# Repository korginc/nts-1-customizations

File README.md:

# nts-1-customizations

Official repository for hardware customizations of the [Nu:Tekt NTS-1 digital kit](https://www.korg.com/nts_1) programmable synthesizer. 

Make your own custom interface using reference schematics, CAD and PCB data, and libraries for the Arduino IDE.

## Repo Content

* _Arduino/package_nts1_custom_panels_index.json_: Arduino IDE package Boards Manager package description file
* _Custom_Panel_RevC/_: Content specific to NTS-1 Custom Panel reference board revision C
  * _Arduino/libraries/_: Arduino IDE libraries
  * _Gerber/_: Raw PCB Gerber data output
  * _KiCAD/_: [KiCAD](https://kicad.org/) project
  * _BOM-mouser.pdf_: Bill of materials with [Mouser](https://www.mouser.com/) part numbers in PDF format
  * _BOM-mouser.xls_: Bill of materials with [Mouser](https://www.mouser.com/) part numbers in XLS format (can be uploaded directly to cart)
  * _Gerber\_reference.pdf_: PCB trace and masks visual reference in PDF format
  * _mount\_diagram.pdf_: Part placement visual reference in PDF format
  * _schematic.pdf_: Circuit diagram in PDF format

## Assembly/Programming

Refer to the [companion web site](https://korginc.github.io/nts-1-customizations) for assembly/programming instructions, examples and further reference.

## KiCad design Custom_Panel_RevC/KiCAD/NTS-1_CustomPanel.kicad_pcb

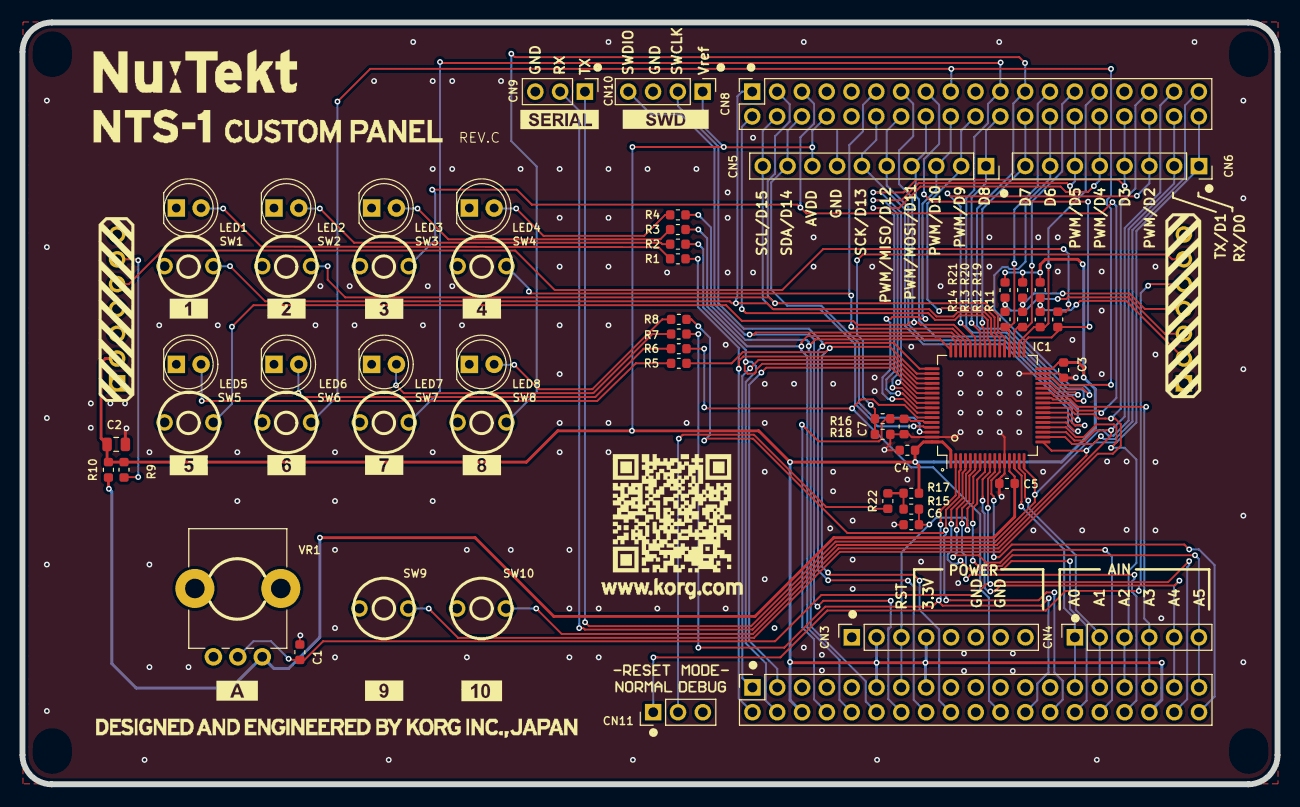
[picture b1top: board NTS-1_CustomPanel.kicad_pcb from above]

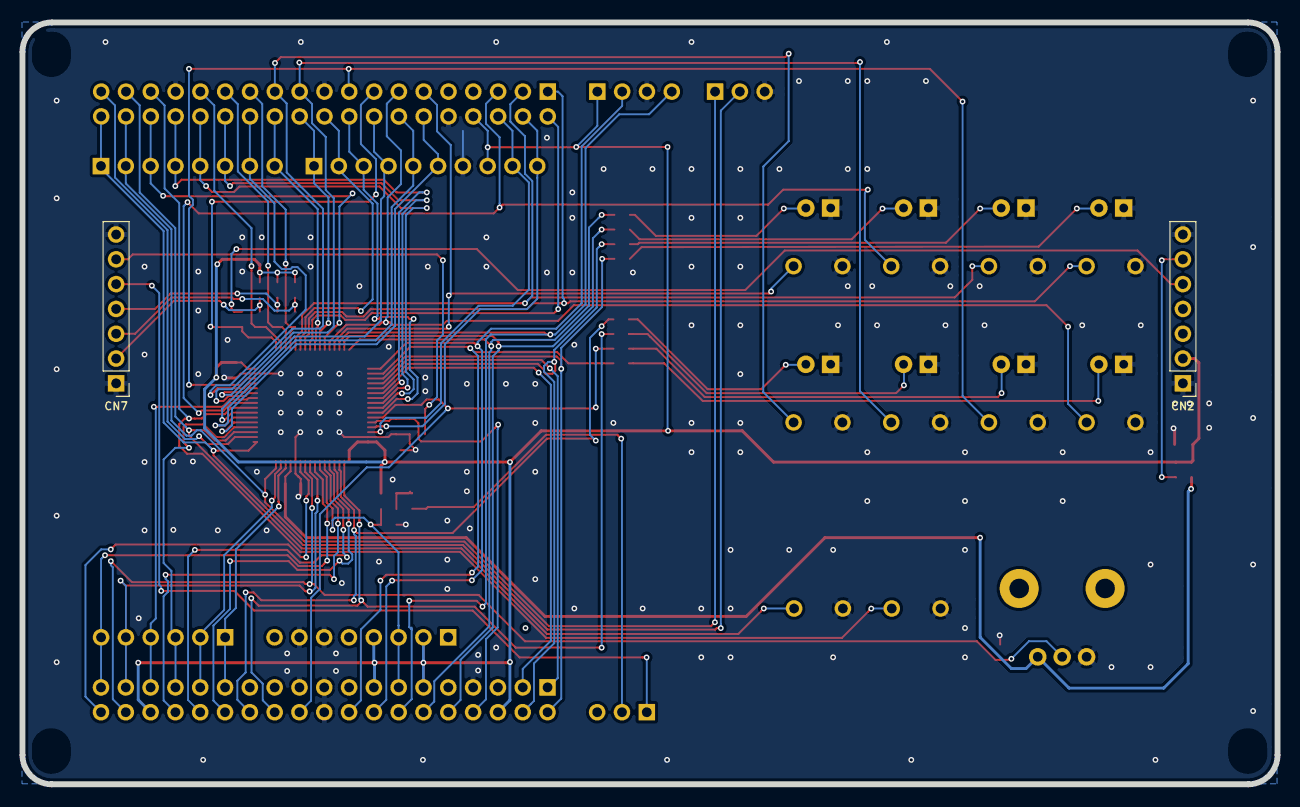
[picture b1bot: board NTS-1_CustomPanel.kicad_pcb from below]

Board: 2 copper layers, 128.5 x 78.0 mm, 60 parts (2 on the bottom side), 77 nets.

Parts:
C1, C3, C4, C5: 0.1u; C_0603_1608Metric
C2: 10u; C_0805_2012Metric
C6, C7: 1000p; C_0603_1608Metric
CN1, CN8: 19x2 2.54mm header; PinSocket_2x19_P2.54mm_Vertical
CN2, CN7: 1x7 2.54mm header; PinHeader_1x07_P2.54mm_Vertical
CN3, CN6: 1x8 2.54mm connector; PinSocket_1x08_P2.54mm_Vertical
CN4: 1x6 2.54mm connector; PinSocket_1x06_P2.54mm_Vertical
CN5: 1x10 2.54mm connector; PinSocket_1x10_P2.54mm_Vertical
CN9, CN11: 1x3 2.54mm header; PinHeader_1x03_P2.54mm_Vertical
CN10: 1x4 2.54mm header; PinHeader_1x04_P2.54mm_Vertical
IC1: STM32F030R8T6; LQFP-64_10x10mm_P0.5mm
LED1, LED2, LED3, LED4, LED5, LED6, LED7, LED8: LED; LED_D5.0mm
R1, R2, R3, R4, R5, R6, R7, R8: 220; R_0603_1608Metric
R9, R19, R20, R21: 10k; R_0603_1608Metric
R10: 0; R_0603_1608Metric
R11, R12, R13, R14: 47; R_0603_1608Metric
R15: 33; R_0603_1608Metric
R16, R22: 1k; R_0603_1608Metric
R17: 100k; R_0603_1608Metric
R18: 47k; R_0603_1608Metric
SW1, SW2, SW3, SW4, SW5, SW6, SW7, SW8, SW9, SW10: TACT SW; SW_Tactile_SKRH
VR1: 10kB; Potentiometer_Alps_RK09K_Single_Vertical

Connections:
+3V3: C2.1, C3.1, C4.1, CN1.6, CN1.11, CN1.15, CN1.34, CN2.2, CN3.2, CN3.4, CN5.8, CN8.8, CN10.1, IC1.1, IC1.32, IC1.64, R9.1, R10.2, R17.1, R19.1, R20.1, R21.1
+3V3Ref: C5.1, IC1.13, R10.1, VR1.1
/BOOT0: C7.1, CN1.8, IC1.60, R16.2
/BOOT_PNL: CN7.6, R16.1, R18.1
/CK_PNL: CN7.2, R12.1, R19.2
/NRST: C6.1, CN1.13, CN3.3, IC1.7, R15.2
/PA0: CN1.27, CN4.1, IC1.14
/PA1: CN1.29, CN4.2, IC1.15
/PA2: CN6.2, CN8.36, CN9.1, IC1.16
/PA3: CN6.1, CN8.38, CN9.2, IC1.17
/PA4: CN1.31, CN4.3, IC1.20
/PA5: CN5.6, CN8.12, IC1.21
/PA6: CN5.5, CN8.14, IC1.22
/PA7: CN5.4, CN8.16, IC1.23
/PA8: CN6.8, CN8.24, IC1.41
/PA9: CN5.1, CN8.22, IC1.42
/PA10: CN6.3, CN8.34, IC1.43
/PA11: CN8.13, IC1.44, SW5.1
/PA12: CN8.11, IC1.45, SW4.1
/PA13: CN1.14, CN10.4, IC1.46
/PA14: CN1.16, CN10.2, IC1.49
/PA15: CN1.18, IC1.50, R5.2
/PANEL_ACK: CN2.5, R11.1
/PB0: CN1.33, CN4.4, IC1.26
/PB1: CN8.23, IC1.27, SW8.1
/PB2: CN8.21, IC1.28, SW7.1
/PB3: CN6.4, CN8.32, IC1.55
/PB4: CN6.6, CN8.28, IC1.56
/PB5: CN6.5, CN8.30, IC1.57
/PB6: CN5.3, CN8.18, IC1.58
/PB7: CN1.22, IC1.59, R6.2
/PB8: CN5.10, CN8.4, IC1.61
/PB9: CN5.9, CN8.6, IC1.62
/PB10: CN6.7, CN8.26, IC1.29
/PB11: CN8.17, IC1.30, SW6.1
/PB12: CN8.15, IC1.33, R11.2
/PB13: CN8.29, IC1.34, R12.2
/PB14: CN8.27, IC1.35, R13.2
/PB15: CN8.25, IC1.36, R14.2
/PC0: CN1.37, CN4.6, IC1.8
/PC1: CN1.35, CN4.5, IC1.9
/PC2: C1.1, CN1.36, IC1.10, VR1.2
/PC3: CN1.38, IC1.11
/PC4: CN8.33, IC1.24, SW9.1
/PC5: CN8.5, IC1.25, SW3.1
/PC6: CN8.3, IC1.37, SW2.1
/PC7: CN5.2, CN8.20, IC1.38
/PC8: CN8.1, IC1.39, SW1.1
/PC9: CN8.2, IC1.40
/PC10: CN1.2, IC1.51, R1.2
/PC11: CN1.1, IC1.52
/PC12: CN1.4, IC1.53, R2.2
/PC13: CN1.24, IC1.2, R7.2
/PC14: CN1.26, IC1.3, R8.2
/PC15: CN1.28, IC1.4
/PD2: CN1.3, IC1.54
/PF0: CN1.30, IC1.5
/PF1: CN1.32, IC1.6
/PF4: CN8.37, IC1.18
/PF5: CN8.35, IC1.19, SW10.1
/PF6: CN1.10, IC1.47, R3.2
/PF7: CN1.12, IC1.48, R4.2
/RX_PNL: CN7.3, R14.1, R21.2
/TX_PNL: CN7.4, R13.1, R20.2
/~RESET_PNL: CN7.5, CN11.1
GND: C1.2, C2.2, C3.2, C4.2, C5.2, C6.2, C7.2, CN1.7, CN1.19, CN1.20, CN1.21, CN2.1, CN2.7, CN3.6, CN3.7, CN5.7, CN7.1, CN7.7, CN8.10, CN8.19, CN8.31, CN9.3, CN10.3, IC1.12, IC1.31, IC1.63, LED1.1, LED2.1, LED3.1, LED4.1, LED5.1, LED6.1, LED7.1, LED8.1, R18.2, SW1.2, SW2.2, SW3.2, SW4.2, SW5.2, SW6.2, SW7.2, SW8.2, SW9.2, SW10.2, VR1.3
unnamed: CN2.6, R9.2
unnamed: CN11.2, R22.1
unnamed: LED1.2, R1.1
unnamed: LED2.2, R2.1
unnamed: LED3.2, R3.1
unnamed: LED4.2, R4.1
unnamed: LED5.2, R5.1
unnamed: LED6.2, R6.1
unnamed: LED7.2, R7.1
unnamed: LED8.2, R8.1
unnamed: R15.1, R17.2, R22.2

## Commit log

2020-01-08 Add basic .gitignore
2020-01-08 Add issue templates.
2020-01-08 Add initial web files.
2020-01-08 Fix typo.
2020-01-08 Restructure pages.
2020-01-08 Make site title shorter.
2020-01-08 Update reference
2020-01-08 Add placeholder for reference panel design rev.B
2020-01-08 Add some image assets and rewrite indexes.
2020-01-08 Fix broken link
2020-01-08 Rewrite programming page.
2020-01-08 Fix blockquotes.
2020-01-08 Remove bold.
2020-01-08 Reorganize sections. Remove mini STLINK reference. Other minor fixes.
2020-01-08 Rewrite quickstart as assembly.
2020-01-08 Rename firmware as examples and delete remaining quickstart.
2020-01-08 Add assembly heading.
2020-01-08 Fix image paths.
2020-01-08 Uniformize headings.
2020-01-08 Rewrite index.
2020-01-08 Tweak getting started list.
2020-01-08 Make getting started header bigger
2020-01-08 Make getting started header bigger (ja)
2020-01-08 Fix note capitalization and spacing.
2020-01-08 Add link to github repository.
2020-01-08 Add examples outline.
2020-01-08 Draft reference structure.
2020-01-08 Fix merged notes.
2020-01-08 Add section for user oscillator editor board.
2020-01-08 Add image of bare board with parts.
2020-01-08 Add SWD connection and Serial monitor connection images.
2020-01-08 Move bare board and parts image below acquiring parts section.
2020-01-08 Rename revB folder.
2020-01-08 Add hardware files.
2020-01-08 Fix wrong layout on some japanese pages.
2020-01-08 Add links for hardware files.
2020-01-08 Add PDF version of BOM.
2020-01-08 Update hardware file links and update ja version.
2020-01-08 Add repo clone and zip file download hints.
2020-01-08 Simplify.
2020-01-08 Add minimal info about arduino sketch examples.
2020-01-08 Add Arduino IDE success outputs.
2020-01-09 Remove old comments.
2020-01-09 Move clone/download comments into hardware section.
2020-01-09 [revB][arduino] Add example template Sketches.
2020-01-09 Add READMEs to arduino templates.
2020-01-09 Add proper headers with license info.
2020-01-09 Relicense blank template to the unlicense since it barely contains anything and requiring the BSD disclaimer to be retained would be pointlessly encumbering.
2020-01-09 Add link to arduino example sketches in github repo.
2020-01-09 Add direct link to code for arduino sketch examples.
2020-01-09 Replace XLS by Excel.
2020-01-09 Add BOM in table format and links to the PDF and Excel files.
2020-01-09 [revB] Remove japanese column name from BOM, re-export PDF with all columns.
2020-01-09 Change BOM PDF link to raw direct link since github preview is too small to read.
2020-01-09 Make full BOM links and comments more visible.
2020-01-09 Minor formating tweaks.
2020-01-09 Remove old comments and improve intro copy for reference design.
2020-01-09 Refocus copy on PCB/design resources.
2020-01-09 Fix capitalization of GitHub
2020-01-09 [revB] Add gerber reference and mount diagram PDFs.
2020-01-09 Add soldering tutorials links. Add links to schematic and mount diagram.
2020-01-09 Remove redundancy.
2020-01-09 Improve reference board index image. Add images for demo custom panels.
2020-01-09 Fix broken product link
2020-01-09 Fix URLs after renaming repository.
2020-01-09 Fix github link in home footer. Fix old logue-sdk url.
2020-01-09 Add details to demo boards.
2020-01-09 Reoarder images and details in demo boards.
2020-01-09 Fix naming of Nucleo expansion connectors.
2020-01-10 Move and tweak caution about 3.3V/5V serial adapters.
2020-01-10 Rev.B data was actually Rev.C, fix some conflicting info in KiCAD files.
2020-01-10 Change encoding to utf-8-unix
2020-01-10 Remove overexplicit mentions of board revision. Fix remaining mention of RevB board.
2020-01-10 Add Arduino boards index.
2020-01-10 GitHub pages does not seem to serve json files. Rename to txt.
2020-01-10 Test serving a simple text file.
2020-01-10 Test serving text file from subdir
2020-01-10 Move arduino boards index to assets.
2020-01-10 Remove file extension on arduino_boards to see if it gets served. Remove test bar.txt file.
2020-01-10 Remove arduino boards index since it wont be served by jekyll no matter the file name and location.
2020-01-10 Add Arduino boards index file.
2020-01-10 Fix wrong size of board package.
2020-01-10 Update URL for arduino boards json file.
2020-01-10 Rename Arduino boards index file to common format.
2020-01-10 Update arduino boards index URL
2020-01-10 Rename arduino board platform.
2020-01-10 Revert name of arduino board platform.
2020-01-10 Update Arduino board package url, hash and size.
2020-01-10 Update Arduino board package website URL and online help URL
2020-01-10 Fix Arduino board online help URL
2020-01-10 Update Arduino board hash and size.
2020-01-10 Change packager for tools in order to remove dependency on STM32 package.
2020-01-10 [revC] Replace examples with full NTS-1 board library.
2020-01-10 Change URLs and guidance for Arduino board definition, libraries and examples.
2020-01-10 Fix NTS-1 library repo URL
2020-01-10 Remove install step for STM32Cores package.
2020-01-10 Add link for NTS1 class definition.
2020-01-10 Add youtube include for video embeds
2020-01-10 Add youtube include variant for autoplay.
2020-01-10 Add video to home page.
2020-01-10 Add autoplay / modestbranding attributes where needed
2020-01-10 Fix home page youtube video size.
2020-01-10 Quote youtube include attributes.
2020-01-10 Make home page video slightly bigger.
2020-01-10 Disable autoplay on home page video
2020-01-10 Add assembly video
2020-01-10 Add demo videos.
2020-01-13 [revC] Lower power stabilizing capacitor to 1u.
2020-01-13 Change power stabilizing capacitor to 1uF.
2020-01-14 Fix alignment of pcb image.
2020-01-14 Adjust video sizes.
2020-01-14 Add japanese translation and remove a few old notes.
2020-01-14 Comment out unfinished reference content.
2020-01-14 Tweak site description copy.
2020-01-15 Add more details to top-level README.
2020-01-15 Fix URL and shorten some content descriptions.
2020-01-15 [revC][arduino] Add more details to NTS1 class definition doc.
2020-01-15 [revC][arduino] Add type definitions for rx message handlers and remove extraneous colons.
2020-01-15 Link directly to README for NTS1 class def. (ja)
2020-01-15 Link directly to README for NTS1 class def.
2020-01-15 Fix bullet list
2020-01-15 Fix example links
2020-01-21 Postpone estimated release date for 1.10 firmware. Fix link.
2020-02-14 Reencode to unix format.
2020-02-14 [revC][arduino] Fix param sub-id syntax.
2020-02-14 [revC][arduino] Add nts1_iface.h/.c from board variant for reference.
2020-02-14 [arduino] Update arduino package index JSON: add v1.0.1 package.
2020-02-14 [revC][arduino] Update NTS1 class reference with changes for v1.0.1
2020-02-14 [revC][arduino] Fix format for some params.
2020-02-14 [arduino] Fix URL for 1.0.1 package indedx.
2020-02-14 [revC][arduino] Fix include in code example to match v1.0.1.
2020-02-14 Add explicit link to github repo.
2020-09-06 slow down the clock of GPIO pins for SPI
2020-09-13 fix: add aligned atrtribute to s_rx_event_decode_buf
2021-11-08 Update README.md
    https://forum.kicad.info/t/warning-avoid-all-links-to-kicad-pcb-org-use-kicad-org/31521
